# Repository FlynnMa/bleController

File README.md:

## BLE code integrates linkmagic protocol

##HARDWARE

nRF51822

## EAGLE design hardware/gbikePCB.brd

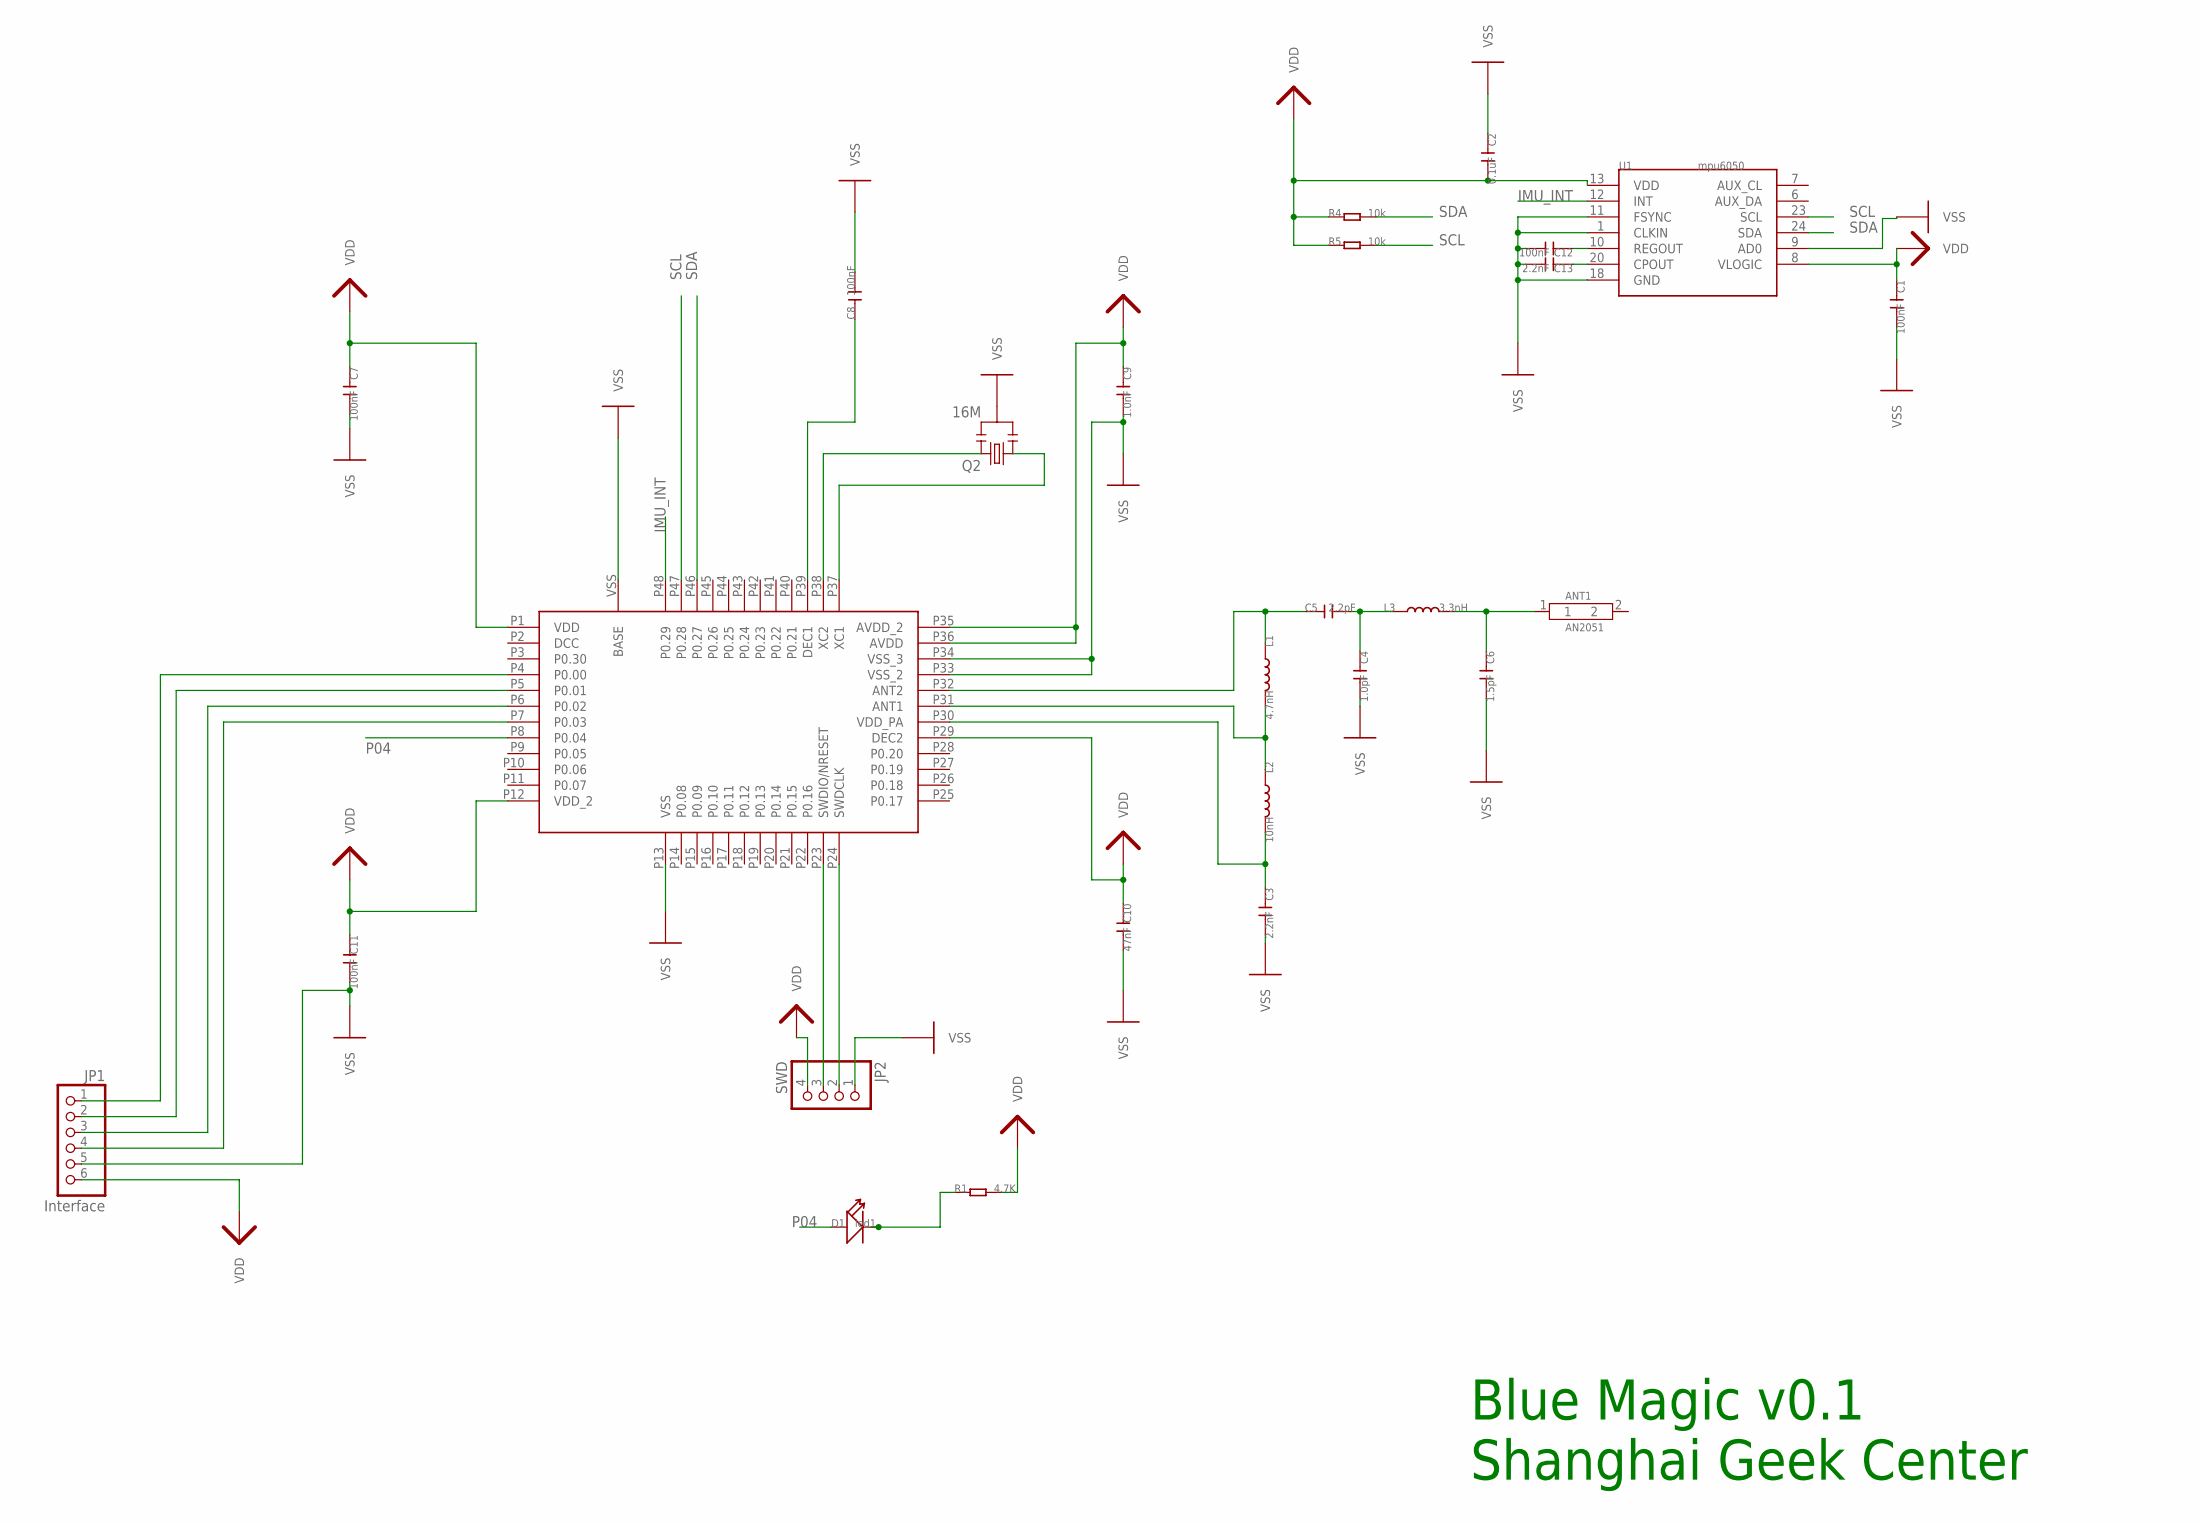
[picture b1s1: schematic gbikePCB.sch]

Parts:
ANT1: AN2051; CONNECTOR_2P-SMD-L5.05*W.02*H1.07MM
C1, C7, C8, C11, C12: 100nF; DISCRETE_C0603
C2: 0.1uF; DISCRETE_C0603
C3, C13: 2.2nF; DISCRETE_C0603
C4: 1.0pF; DISCRETE_C0603
C5: 2.2pF; DISCRETE_C0603
C6: 1.5pF; DISCRETE_C0603
C9: 1.0nF; DISCRETE_C0603
C10: 47nF; DISCRETE_C0603
D1: led1; DISCRETE_LED-0603
JP1: Interface; 1X06
JP2: SWD; 1X04
L1: 4.7nH; DISCRETE_L0603
L2: 10nH; DISCRETE_L0603
L3: 3.3nH; DISCRETE_L0603
NRF51822: nRF51822; NRF51822_NRF51822_QFN48
Q2: 16M; DIYDRONES3_RESONATOR-SMD
R1: 4.7K; DISCRETE_R0603
R4, R5: 10k; DISCRETE_R0603
U1: mpu6050; TINY_BLE_V1.0_TEMPLATE_QFN24

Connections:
IMU_INT: NRF51822.P48 (P0.29), U1.12 (INT)
unnamed: JP1.1, NRF51822.P4 (P0.00)
unnamed: C3.1, L2.2, NRF51822.P30 (VDD_PA)
unnamed: NRF51822.P38 (XC2), Q2.3
unnamed: C8.1, NRF51822.P39 (DEC1)
unnamed: C5.1, L1.1, NRF51822.P32 (ANT2)
unnamed: C4.1, C5.2, L3.1
unnamed: ANT1.1, C6.1, L3.2
unnamed: NRF51822.P37 (XC1), Q2.1
unnamed: JP1.2, NRF51822.P5 (P0.01)
unnamed: JP1.3, NRF51822.P6 (P0.02)
unnamed: L1.2, L2.1, NRF51822.P31 (ANT1)
unnamed: JP1.4, NRF51822.P7 (P0.03)
unnamed: D1.-, R1.1
unnamed: C12.1, U1.10 (REGOUT)
unnamed: C13.1, U1.20 (CPOUT)
unnamed: JP2.3, NRF51822.P23 (SWDIO/NRESET)
unnamed: JP2.2, NRF51822.P24 (SWDCLK)
P04: D1.+, NRF51822.P8 (P0.04)
SCL: NRF51822.P47 (P0.28), R5.2, U1.23 (SCL)
SDA: NRF51822.P46 (P0.27), R4.2, U1.24 (SDA)
VDD: C1.1, C2.2, C7.1, C9.1, C10.1, C11.1, JP1.6, JP2.4, NRF51822.P1 (VDD), NRF51822.P12 (VDD_2), NRF51822.P29 (DEC2), NRF51822.P35 (AVDD_2), NRF51822.P36 (AVDD), R1.2, R4.1, R5.1, U1.8 (VLOGIC), U1.13 (VDD)
VSS: C1.2, C2.1, C3.2, C4.2, C6.2, C7.2, C8.2, C9.2, C10.2, C11.2, C12.2, C13.2, JP1.5, JP2.1, NRF51822.P13 (VSS), NRF51822.P33 (VSS_2), NRF51822.P34 (VSS_3), NRF51822.VSS (BASE), Q2.2, U1.1 (CLKIN), U1.9 (AD0), U1.11 (FSYNC), U1.18 (GND)

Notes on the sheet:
Blue Magic v0.1 Shanghai Geek Center

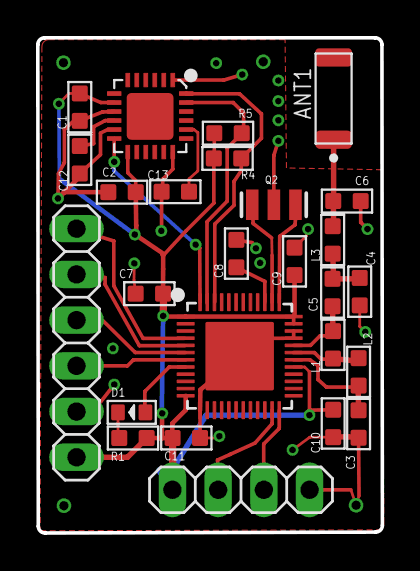
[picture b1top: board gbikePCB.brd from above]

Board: 2 copper layers, 19.1 x 27.5 mm, 26 parts (0 on the bottom side), 23 nets.

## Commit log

2015-08-25 add LICENSE
2015-09-20 add pcb file, be aware ! this pcb file has not been certified !!!
2015-10-03 updated pcb file
2020-09-08 add readme
